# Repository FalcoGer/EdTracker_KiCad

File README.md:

# EdTracker_KiCad
Schematics for an EdTracker (DIY)  
Get software (Arduino firmware sources, documentation, precompiled firmware and windows ui program) from https://github.com/brumster/EDTracker2  
Get special arduino hardware libraries from https://github.com/brumster/EDTracker2_ArduinoHardware

Front:  

Back:

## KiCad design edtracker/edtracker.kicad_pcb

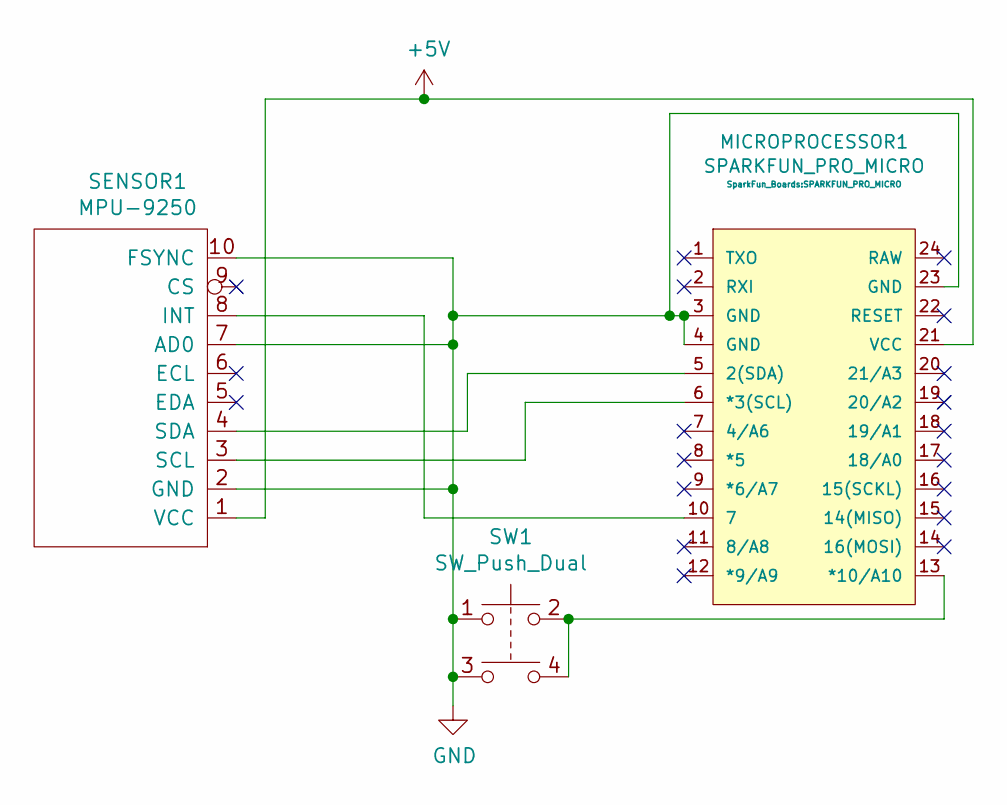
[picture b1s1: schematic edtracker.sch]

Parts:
MICROPROCESSOR1: SPARKFUN_PRO_MICRO
SENSOR1: MPU-9250
SW1: SW_Push_Dual; SW_PUSH_6mm_Dual

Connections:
+5V: MICROPROCESSOR1.21 (VCC), SENSOR1.1 (VCC)
GND: MICROPROCESSOR1.3 (GND), MICROPROCESSOR1.4 (GND), MICROPROCESSOR1.23 (GND), SENSOR1.2 (GND), SENSOR1.7 (AD0), SENSOR1.10 (FSYNC), SW1.1, SW1.3
unnamed: MICROPROCESSOR1.5 (2(SDA)), SENSOR1.4 (SDA)
unnamed: MICROPROCESSOR1.6 (*3(SCL)), SENSOR1.3 (SCL)
unnamed: MICROPROCESSOR1.10 (7), SENSOR1.8 (INT)
unnamed: MICROPROCESSOR1.13 (*10/A10), SW1.2, SW1.4

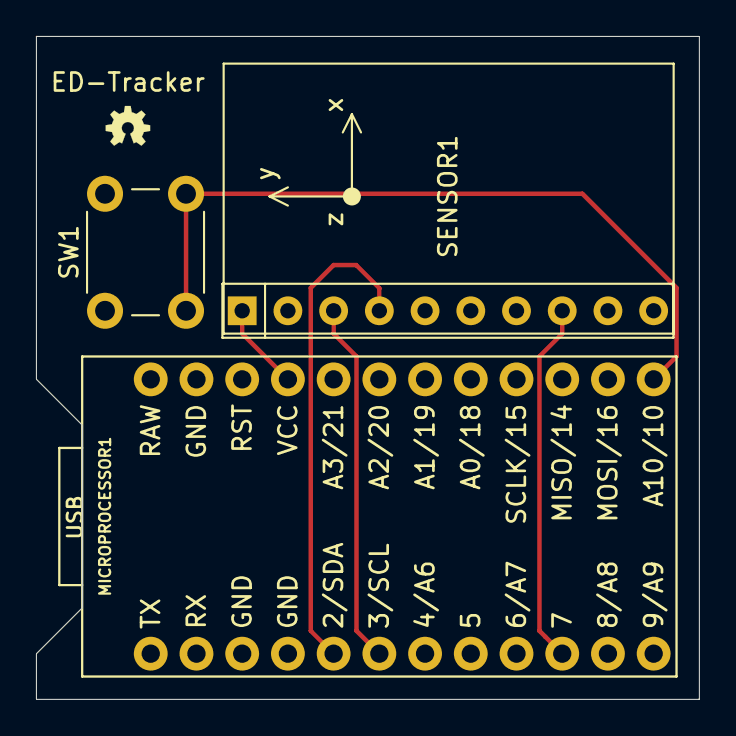
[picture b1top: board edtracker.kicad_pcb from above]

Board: 2 copper layers, 36.8 x 36.8 mm, 3 parts (0 on the bottom side), 6 nets.

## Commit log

2021-01-22 update gitignore
2021-01-22 added edtracker kicad files
2021-01-22 fixed missing fill for ground plane
2021-01-22 added gerber and drill files
2021-01-22 fix wrong footprint (silk F overlap) for promicro updated gerber files with fix
2021-01-22 updated footprint for mpu-9250
2021-01-22 changed processor -> microprocessor updated silkscreen
2021-01-23 added script to automatically generate gerber and drill files
2021-01-23 added eco1 and eco2 layers gerber files (though unused for this project)
2021-01-23 Added open hardware logo and link to repo
2021-01-23 set invisible text in gerber generator to false removed invisible text from gerber files
2021-01-23 updated readme with images and links to software repos
2021-01-23 fix images
2021-01-23 added GerberRender submodule updated images using the renderer
2021-01-23 added 5v power port
2021-01-24 connected fsync to ground according to mpu spec
